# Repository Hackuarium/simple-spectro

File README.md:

# DIY spectrophotometer

## How to use it ?

Please check the [userguide](docs/5-use) to obtain all the useful information about the user interface.

## Goal of the project

This project was done at the [Hackuarium](http://www.hackuarium.ch/en/) association, a DIY biology hacking-space and open laboratory located in Ecublens (Switzerland). Feel free to [contact us](https://form.jotformeu.com/71600609780354) if you would like additional information or would like to buy a fully built and tested spectrophotometer.

Recently, the open-source and open-hardware community has been involved in the creation of open scientific tools. In this context, a few spectrophotometer projects emerged. However, none of them was sufficiently evolved to be casually used in a laboratory. It is for this reason that we started this project.
Our goal was to create a simple spectrophotometer that measures the
absorbance of a sample for 3 different light colors (red, green, blue), that is
self-contained (battery powered) and displays the result on a LCD screen. In addition, the tool had to be reliable, precise and cheap.

The initial idea was that you could teach spectrophotometry without
having to buy an expensive instrument, since you can find experiments
that do not require a specific light wavelength. This includes
optical density for bacteria culture, determination of a pigment's concentration in
a solution, determination of the kinetic of a reaction and many others.

The device is rather cheap, for you can buy all the components on AliExpress
(but one) and either 3D print or laser cut the case (MDF or acrylic glass). When constructing 10, the price
per spectrophotometer is around $30. However if you want to have a final
product with an aluminium case and PCBs already assembled, the cost would rather be $90 each if you order 20 of them.

## Can we do science with this ?

Before trying to explain how it is done more in detail maybe the first
question that we should answer is : can we do science with this tool?
When thinking about the design of the spectro, we found an light sensor that converts the light energy to frequency and that is linear on a range of nearly 10^6. This means that the luminosity range that we can measure precisely is really big. Only the precision of the component is therefore really promising and shows that we could do something that gives good results.

And indeed, the final product gives really accurate results in fields like:

- [Chemistry](docs/6-applications/chemistry/README.md)
- [Biology](docs/6-applications/biology/README.md)

And other, which you can see on [our lab notebook](experiments/README.md).

## Some of our results

### Patent blue V

To begin we did a very simple experiment that allows to measure the absorbance of solutions containing different known concentrations of patent blue V (E131), a blue pigment that is used in various blue candies.

The result is rather good knowing that the solutions were simply prepared by adding various volumes (0 to 2 mL) of a concentrated pigmented solution with a 1mL seringe to 100mL of water. Not the most accurate method...

### Escherichia coli

Another feature of the simple-spectrophotometer is that it works on a rechargeable battery (autonomy of 48 hours). Consequently, you can measure a kinetic by placing the device directly inside an incubator, which is not feasible with a regular commercial spectrophotometer.

Optical density (OD) at 600nm is often used in biology to determine the biomass increase versus time. In this experiment we have placed Escherichia coli with cell growing media directly in the spectrophotometer cuvette and placed the spectrophotometer itself on a shaker in the incubator.
We can then program it to measure the absorbance every X seconds. In our case we measured the absorbance every 30 minutes (up to 40 measures). The following curve was obtained.

This experiment clearly shows the log phase and the stationary phase. But the growth was faster than expected. An acquisition every 15 minutes would have been a better choice.

## Using the simple spectrophotometer to teach science

The use of the spectrophotometer is rather simple. Just put a blank, press the button, wait 10s and put the sample. The result is displayed on the screen. In addition, it could be open so that students could see how it is inside and could really understand how the tool works (avoiding the "black box" effect). Also, since it is inexpensive, having ten of these for a classroom would be possible, which would allow students to have one instrument per pair.

[Using the spectrophotometer](https://www.youtube.com/watch?v=ZfckWQn0Nws)

For all this reason, we also consider our instrument as a pedagogical tool. This allowed us to use it to teach some basic scientific concepts to groups of children and teenagers.

[School in Mondomo (Colombia)](https://www.youtube.com/watch?v=Be6p4-nW06k)

## How to make it ?

The electronic design is compatible with the Arduino platform. We use an
ATMEGA32U4 microcontroller which is directly connected to the peripherals we need for this spectrophotometer.

We prefer to design the full PCB rather than to make a shield for an existing Arduino board. Indeed, the extra work to add the microcontroller is rather limited, so it does not make sense from our point of view to create a shield. Also, the resulting board is smaller and more reliable.

All the components we use but one are mainstream and can be found on eBay or AliExpress. The only special component is the light to frequency converter [TSL235R](https://www.sparkfun.com/datasheets/Sensors/Imaging/TSL235R-LF.pdf)
that we buy on [Mouser website](http://www.mouser.com).

For more details about the construction process, follow one of the links underneath.

- [The PCB](docs/1-pcb) (using eagle)
- [The case](docs/2-case) (using FreeCAD and OpenSCAD)
- [The software](docs/3-software) (using Arduino)

## Experiments

- [Bacteria growth](experiments/bacteria/README.md)
- [Pigment concentration](experiments/color/README.md)
- [Measure of the fluorescence](experiments/fluorescence/README.md)
- [Kinetic of a reaction](experiments/kinetic/README.md)

## Tests

Underneath, you will find some of the tests we have run to verify the quality of our spectrophotometer.

- [Battery](docs/4-tests/battery)
- [Reproducibility of results](docs/4-tests/stability)

# Workshop

We regularly organize one day workshops "Build your own spectrophotometer" during which the participants learn all the process we went through to obtain the final product and build their own spectrophotometer. Please [contact us](https://form.jotformeu.com/71600609780354) if you are interested by this kind of workshop.

Here are the slides of the presentation we make during the workshop.

- [Slides](docs/7-misc/workshop/slides.pdf)

## Cloning the project

This project uses SUBMODULES.

In order to clone it use:

`git clone --recurse-submodules https://github.com/hackuarium/simple-spectro`

To update the submodules:

`git submodule update --recursive --remote`

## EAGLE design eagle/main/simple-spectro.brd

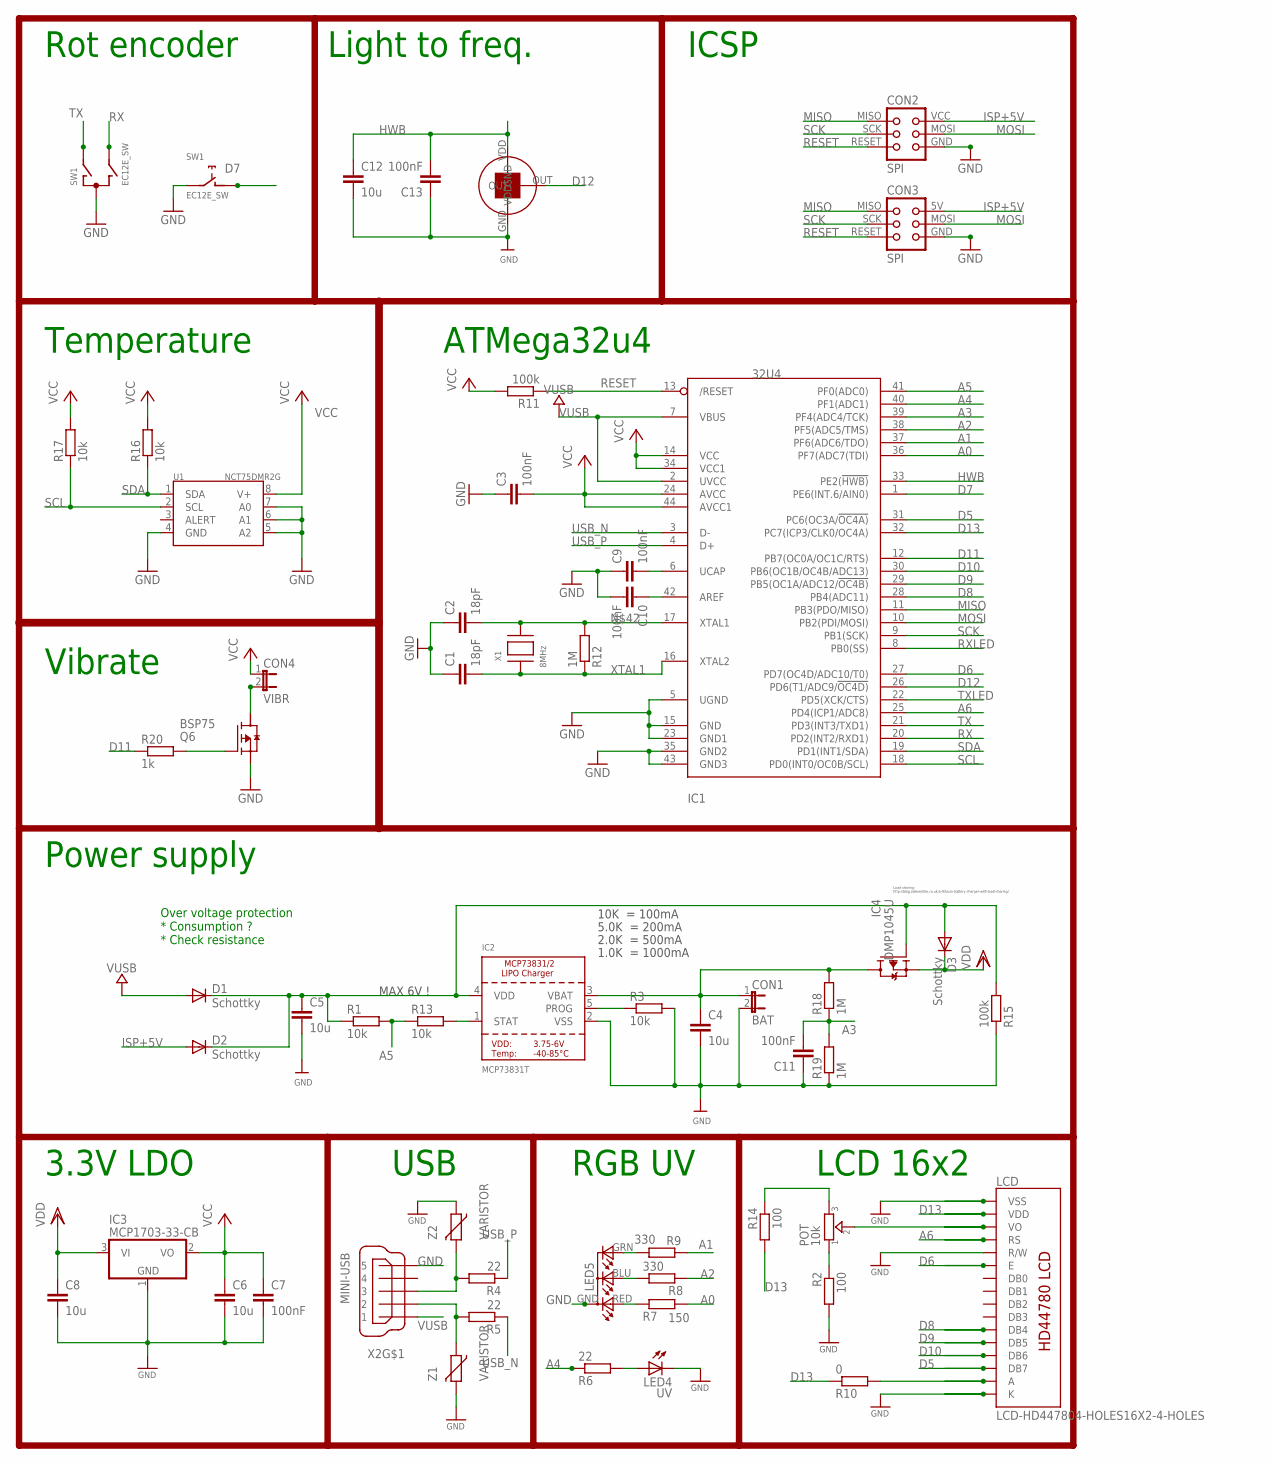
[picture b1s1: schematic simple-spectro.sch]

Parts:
C1, C2: 18pF; C0805K; MPN 77-VJ1206A180JXXPBC; LCSC C1797
C3, C7, C9, C10, C11, C13: 100nF; C0805K; MPN 80-C1206C104K5R; LCSC C49678
C4, C5, C6, C8, C12: 10u; C0805K; MPN 77-VJ1206V106ZXQTBC; LCSC C15850
CON1: BAT; JP1
CON2: SPI; TINYISP
CON3: SPI; TC2030-MCP-NL
CON4: VIBR; JP1
D1, D2, D3: Schottky; SOD123; MPN 621-1N5819HW-F; LCSC C82544
IC1: 32U4; TQFP44; MPN 556-ATMEGA32U4RC-AU; LCSC C44854
IC2: MCP73831T; SOT23-5; MPN 579-MCP73831T-3ACIOT; LCSC C14879
IC3: MCP1703-33-CB; SOT23; LCSC C53352
IC4: DMP1045U; SOT-23; MPN 621-DMP1045U-7; LCSC C110499
LCD: LCD-HD447804-HOLES16X2-4-HOLES; LCD-16X2-4HOLES
LED4: UV; LED5MM
LED5: RGB-COMMON-CATHODE; LED-TRICOLOR-THROUGHHOLE
POT: 10k; TRIMMER_3362P
Q6: BSP75; PG-SOT-223
R1, R3, R13, R16, R17: 10k; R0805; LCSC C17414
R2, R14: 100; R0805; LCSC C17408
R4, R5: 22; R0805; LCSC C17561
R6: 22; R0805; MPN 667-ERJ-8GEYJ101V; LCSC C17561
R7: 150; R0805; LCSC C17513
R8, R9: 330; R0805; LCSC C17513
R10: 0; R0805; LCSC C17477
R11, R15: 100k; R0805; MPN RC1206FR-07100KL; LCSC C17407
R12, R18, R19: 1M; R0805; LCSC C17514
R20: 1k; R0805; LCSC C17513
SW1: EC12E_SW; ALPS_EC12E_SW
U1: NCT75DMR2G; MSOP8; LCSC C94387
U$7: TSL237
X1: 8MHz; NX6035; MPN 729-F60800010; LCSC C122522
X2: MINI-USB; 32005-201; MPN 649-10033526-N3212LF; LCSC C46391
Z1, Z2: VARISTOR; CT/CN0603; LCSC C126845

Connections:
A0: IC1.36 (PF7(ADC7(TDI)), R7.2
A1: IC1.37 (PF6(ADC6/TDO)), R9.1
A2: IC1.38 (PF5(ADC5/TMS)), R8.2
A3: C11.2, IC1.39 (PF4(ADC4/TCK)), R18.1, R19.2
A4: IC1.40 (PF1(ADC1)), R6.1
A5: IC1.41 (PF0(ADC0)), R1.2, R13.1
A6: IC1.25 (PD4(ICP1/ADC8)), LCD.4 (RS)
AREF: C10.1, IC1.42 (AREF)
D5: IC1.31 (PC6(OC3A/!OC4A)), LCD.14 (DB7)
D6: IC1.27 (PD7(OC4D/ADC10/T0)), LCD.6 (E)
D7: IC1.1 (PE6(INT.6/AIN0)), SW1.D (1)
D8: IC1.28 (PB4(ADC11)), LCD.11 (DB4)
D9: IC1.29 (PB5(OC1A/ADC12/!OC4B)), LCD.12 (DB5)
D10: IC1.30 (PB6(OC1B/OC4B/ADC13)), LCD.13 (DB6)
D11: IC1.12 (PB7(OC0A/OC1C/RTS)), R20.1
D12: IC1.26 (PD6(T1/ADC9/!OC4D)), U$7.OUT
D13: IC1.32 (PC7(ICP3/CLK0/OC4A)), LCD.2 (VDD), R10.1, R14.2
GND: C1.1, C2.1, C3.1, C4.2, C5.2, C6.2, C7.2, C8.2, C9.1, C10.2, C11.1, C12.2, C13.1, CON1.2, CON2.GND, CON3.GND, IC1.5 (UGND), IC1.15 (GND), IC1.23 (GND1), IC1.35 (GND2), IC1.43 (GND3), IC2.2 (VSS), IC3.1 (GND), LCD.1 (VSS), LCD.5 (R/W), LCD.16 (K), LED4.K (C), LED5.GND (A2), Q6.3 (S), R2.2, R3.2, R15.1, R19.1, SW1.C, SW1.E (2), U1.4 (GND), U1.5 (A2), U1.6 (A1), U1.7 (A0), U$7.GND, X2.5, Z1.2, Z2.1
HWB: C12.1, C13.2, IC1.33 (PE2(!HWB)), U$7.VDD
ISP+5V: CON2.VCC, CON3.5V (VCC), D2.A
MISO: CON2.MISO, CON3.MISO, IC1.11 (PB3(PDO/MISO))
MOSI: CON2.MOSI, CON3.MOSI, IC1.10 (PB2(PDI/MOSI))
unnamed: C9.2, IC1.6 (UCAP)
unnamed: LCD.3 (VO), POT.2
unnamed: LED4.A, R6.2
unnamed: POT.1, R2.1
unnamed: IC2.1 (STAT), R13.2
unnamed: IC2.5 (PROG), R3.1
unnamed: Q6.1 (G), R20.2
unnamed: LED5.GRN (CGREEN), R9.2
unnamed: LED5.BLU (CBLUE), R8.1
unnamed: LCD.15 (A), R10.2
unnamed: POT.3, R14.1
unnamed: LED5.RED (CRED), R7.1
unnamed: CON4.2, Q6.2 (D)
unnamed: C5.1, D1.C, D2.C, D3.A, IC2.4 (VDD), IC4.1 (G), R1.1, R15.2
unnamed: C2.2, IC1.17 (XTAL1), R12.2, X1.P$2
RESET: CON2.RESET, CON3.RESET, IC1.13 (/RESET), R11.1
RX: IC1.20 (PD2(INT2/RXD1)), SW1.B
RXLED: IC1.8 (PB0(SS))
SCK: CON2.SCK, CON3.SCK, IC1.9 (PB1(SCK))
SCL: IC1.18 (PD0(INT0/OC0B/SCL)), R17.1, U1.2 (SCL)
SDA: IC1.19 (PD1(INT1/SDA)), R16.1, U1.1 (SDA)
TX: IC1.21 (PD3(INT3/TXD1)), SW1.A
TXLED: IC1.22 (PD5(XCK/CTS))
USBC_N: R5.2, X2.2, Z1.1
USBC_P: R4.2, X2.3, Z2.2
USB_N: IC1.3 (D-), R5.1
USB_P: IC1.4 (D+), R4.1
VBAT1: C4.1, CON1.1, IC2.3 (VBAT), IC4.3 (D), R18.2
VCC: C3.2, C6.1, C7.1, CON4.1, IC1.14 (VCC), IC1.24 (AVCC), IC1.34 (VCC1), IC1.44 (AVCC1), IC3.2 (VO), R11.2, R16.2, R17.2, U1.8 (V+)
VDD: C8.1, D3.C, IC3.3 (VI), IC4.2 (S)
VUSB: D1.A, IC1.2 (UVCC), IC1.7 (VBUS), X2.1
XTAL1: C1.2, IC1.16 (XTAL2), R12.1, X1.P$1

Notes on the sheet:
USB
ICSP
ATMega32u4
LCD 16x2
Rot encoder
3.3V LDO
10K = 100mA
5.0K = 200mA
2.0K = 500mA
1.0K = 1000mA
MAX 6V !
Load sharing: http://blog.zakkemble.co.uk/a-lithium-battery-charger-with-load-sharing/
RGB UV
Over voltage protection * Consumption ? * Check resistance
Light to freq.
Power supply
Temperature
Vibrate

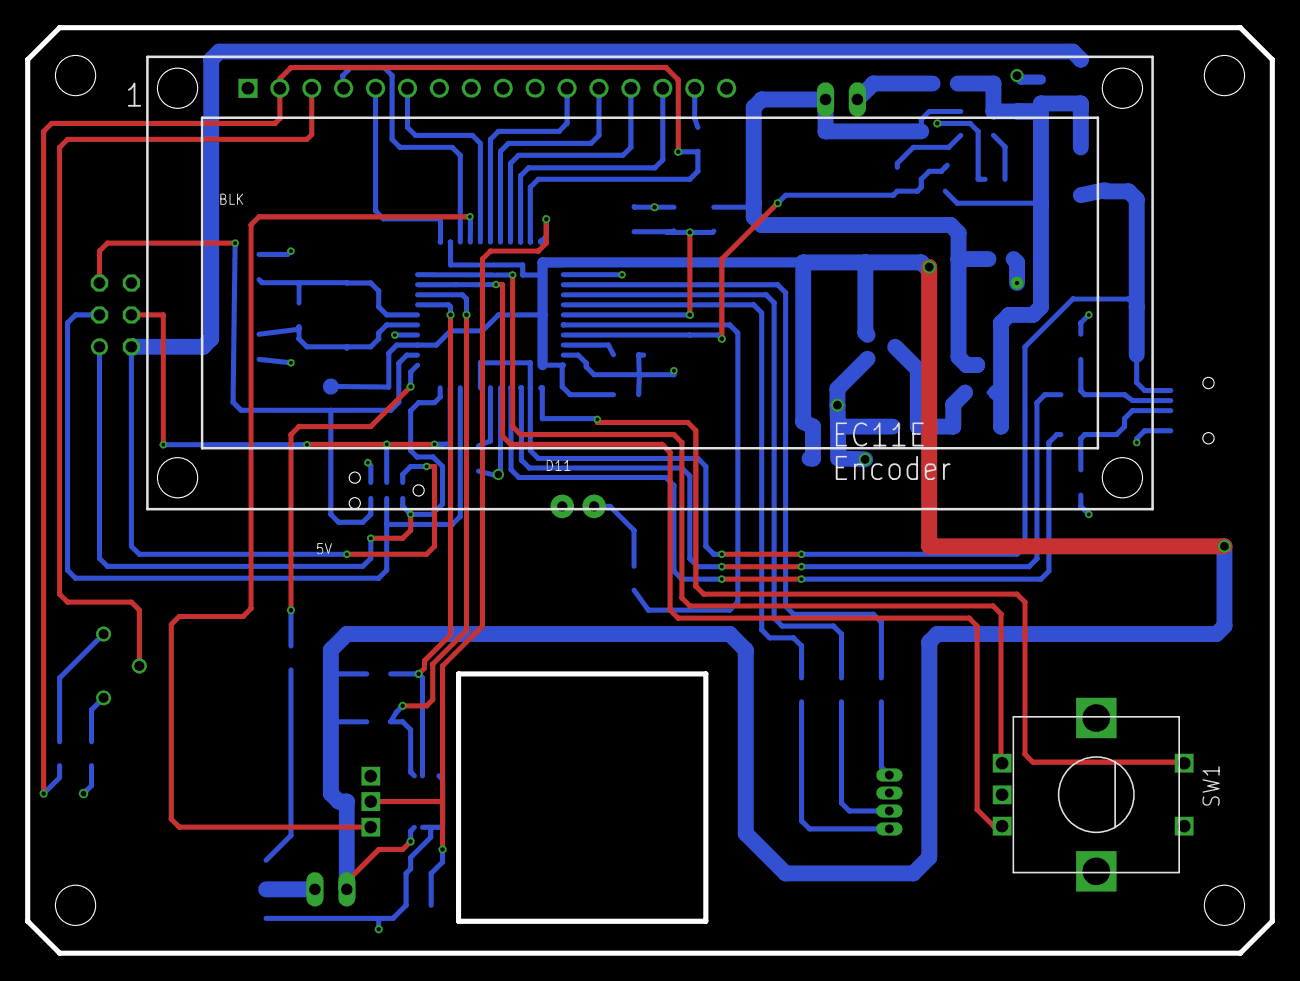
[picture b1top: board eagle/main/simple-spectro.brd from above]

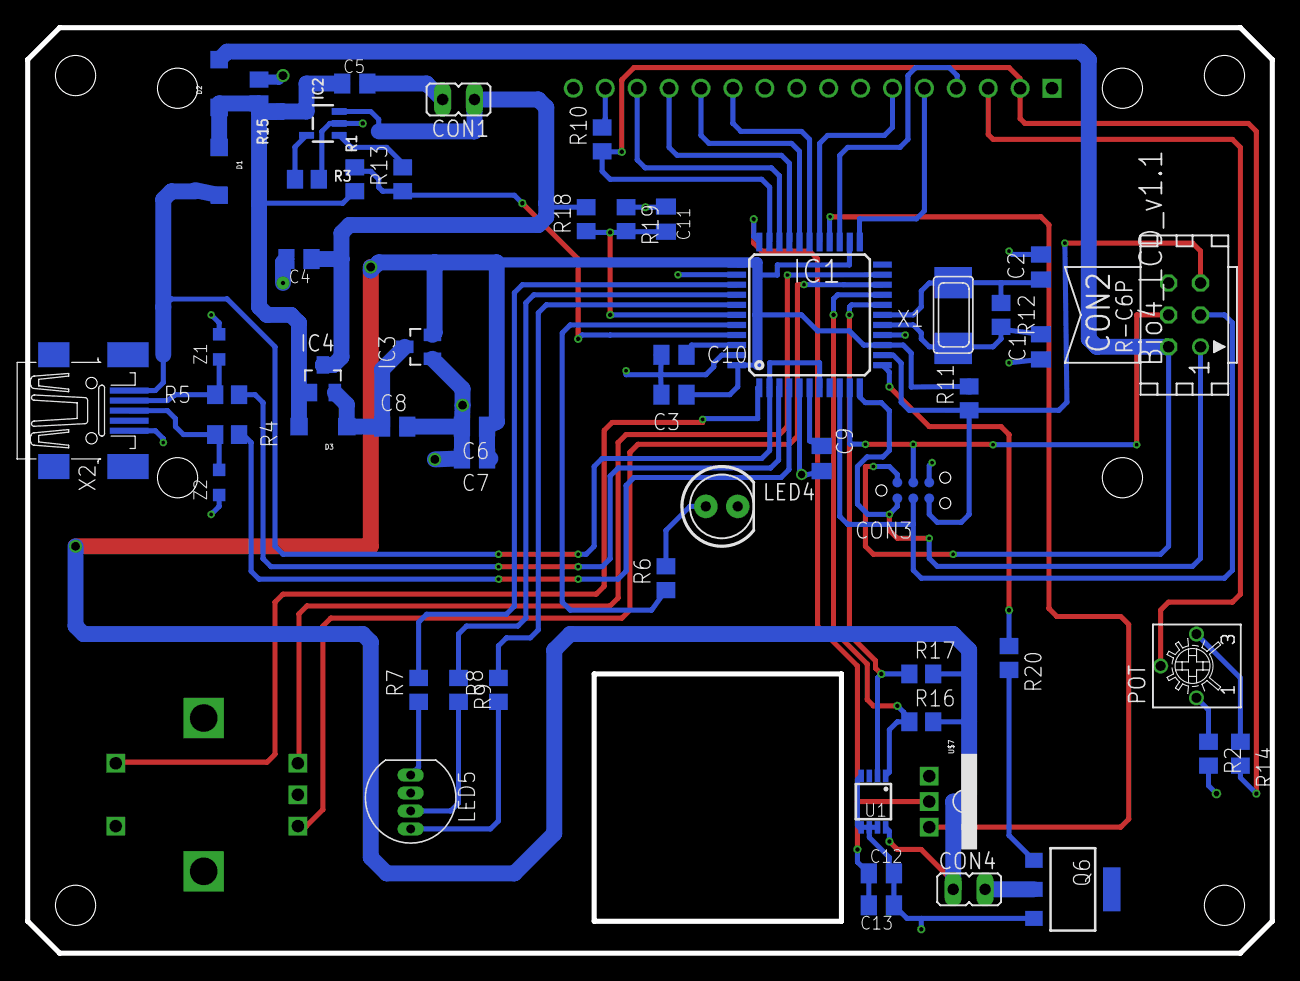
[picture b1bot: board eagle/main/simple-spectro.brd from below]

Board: 2 copper layers, 99.1 x 73.7 mm, 56 parts (54 on the bottom side), 52 nets.

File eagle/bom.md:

| Kind            |  Value         |  Package  |  Qty  |
| ----------------|----------------|-----------|-------  |
| Capacitor       |  100nF         |  1206     |  4  |
| Capacitor       |  10u           |  1206     |  4  |
| Capacitor       |  22pF          |  1206     |  2  |
| Connector       |  BAT           |  2.54mm   |  1  |
| Crystal         |  8MHz          |  6035     |  1  |
| ICSP            |  ICSP          |  2 x 3, 2.54mm  |  1  |
| ICSP            |  TINYISP       |  Tag connect  |  1  |
| Jumper          |  Jumper        |  2.54mm   |  2  |
| LCD             |  LCD-HD447804  |  16x1 2.54mm  |  1  |
| Led             |  GREEN         |  1206     |  1  |
| Led             |  RED           |  1206     |  2  |
| Led             |  RGB-COMMON-CATHODE  |  RGB 5mm led  |  1  |
| Led             |  UV            |  5mm      |  1  |
| Led             |  UV            |  3mm      |  1  |
| Light detector  |  TSL237        |  3x1 2.54mm  |  1  |
| LiPo charger    |  MCP73831T     |  SOT23-5  |  1  |
| Microcontroller |  ATMEGA32U4-AU |  TQFP44  |  1  |
| Mini USB        |  MINI-USB      |  32005-201  |  1  |
| Regulator       |  MCP1703-33    |  SOT223  |  1  |
| Resistor        |  22            |  1206  |  2  |
| Resistor        |  100           |  1206  |  1  |
| Resistor        |  150           |  1206  |  2  |
| Resistor        |  220           |  1206  |  1  |
| Resistor        |  470           |  1206  |  2  |
| Resistor        |  100k          |  1206  |  2  |
| Resistor        |  10k           |  1206  |  2  |
| Resistor        |  1k            |  1206  |  3  |
| Resistor        |  1M            |  1206  |  1  |
| Rotary Encoder  |  EC11E         |  EC11E    |  1  |
| Schottky        |  1N581         |  1206  |  2  |
| Transistor      |  DMP1045U      |  SOT-23  |  1  |
| Trimmer         |  10k           |  3362P  |  1  |

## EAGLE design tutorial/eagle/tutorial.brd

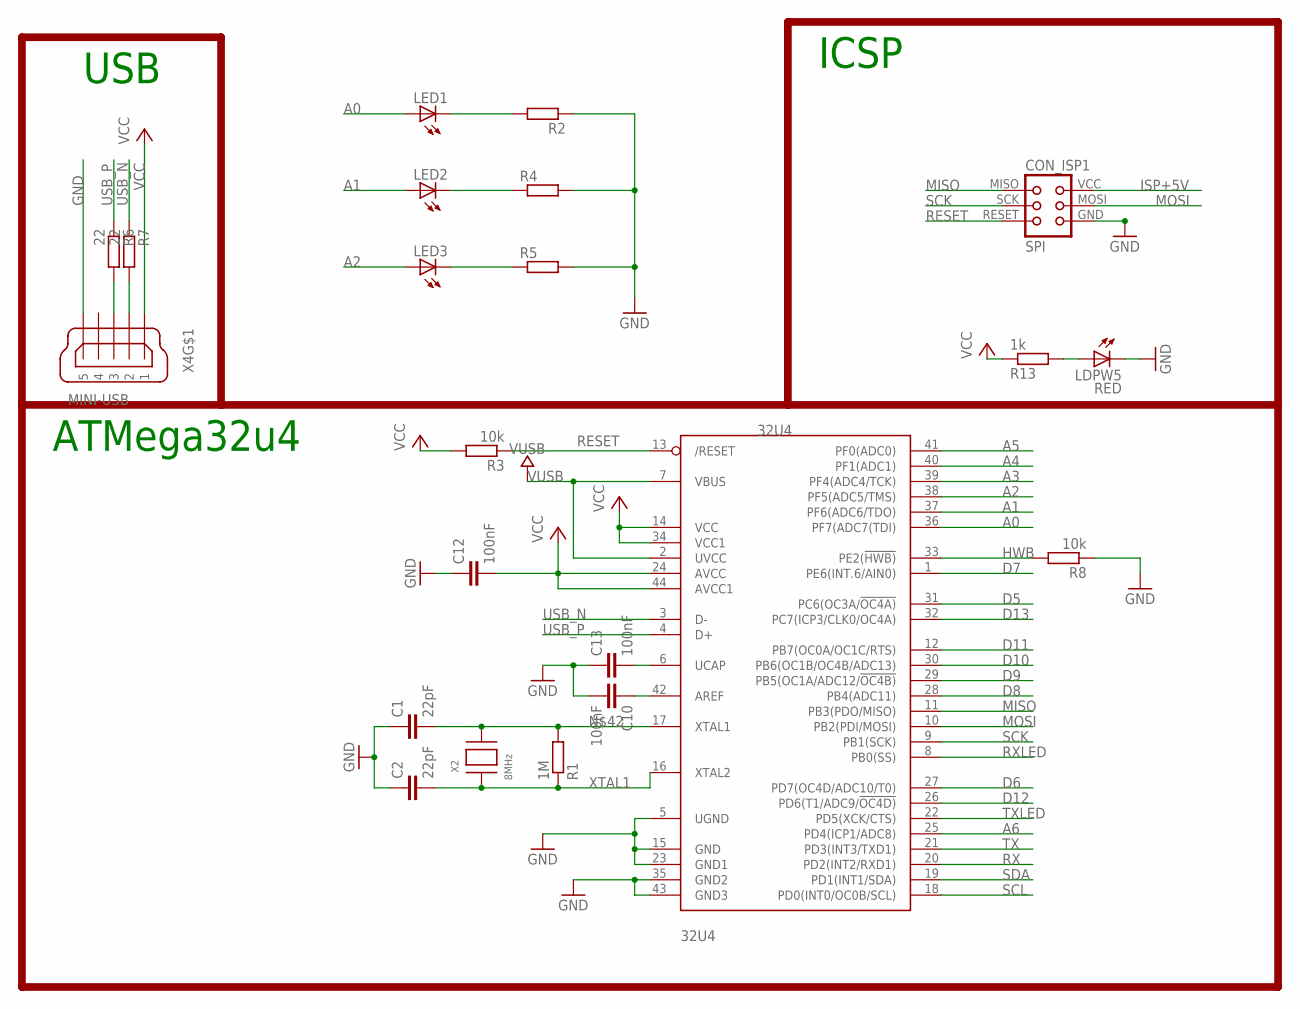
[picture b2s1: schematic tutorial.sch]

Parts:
32U4: 32U4; TQFP44
C1, C2: 22pF; C1206
C10, C12, C13: 100nF; C1206
CON_ISP1: SPI; TINYISP
LDPW5: RED; LED-1206
LED1, LED2, LED3: LED5MM
R1: 1M; M1206
R2: R-EU_R1206; R1206; LCSC 12345
R3, R8: 10k; M1206
R4, R5: R-EU_R1206; R1206
R6, R7: 22; M1206
R13: 1k; M1206
X2: 8MHz; NX6035
X4: MINI-USB; 32005-201

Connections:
A0: 32U4.36 (PF7(ADC7(TDI)), LED1.A
A1: 32U4.37 (PF6(ADC6/TDO)), LED2.A
A2: 32U4.38 (PF5(ADC5/TMS)), LED3.A
A3: 32U4.39 (PF4(ADC4/TCK))
A4: 32U4.40 (PF1(ADC1))
A5: 32U4.41 (PF0(ADC0))
A6: 32U4.25 (PD4(ICP1/ADC8))
AREF: 32U4.42 (AREF), C10.1
D5: 32U4.31 (PC6(OC3A/!OC4A))
D6: 32U4.27 (PD7(OC4D/ADC10/T0))
D7: 32U4.1 (PE6(INT.6/AIN0))
D8: 32U4.28 (PB4(ADC11))
D9: 32U4.29 (PB5(OC1A/ADC12/!OC4B))
D10: 32U4.30 (PB6(OC1B/OC4B/ADC13))
D11: 32U4.12 (PB7(OC0A/OC1C/RTS))
D12: 32U4.26 (PD6(T1/ADC9/!OC4D))
D13: 32U4.32 (PC7(ICP3/CLK0/OC4A))
GND: 32U4.5 (UGND), 32U4.15 (GND), 32U4.23 (GND1), 32U4.35 (GND2), 32U4.43 (GND3), C1.1, C2.1, C10.2, C12.1, C13.1, CON_ISP1.GND, LDPW5.C, R2.1, R4.2, R5.2, R8.1, X4.5
HWB: 32U4.33 (PE2(!HWB)), R8.2
ISP+5V: CON_ISP1.VCC
MISO: 32U4.11 (PB3(PDO/MISO)), CON_ISP1.MISO
MOSI: 32U4.10 (PB2(PDI/MOSI)), CON_ISP1.MOSI
unnamed: 32U4.6 (UCAP), C13.2
unnamed: LED3.K (C), R5.1
unnamed: LED2.K (C), R4.1
unnamed: LED1.K (C), R2.2
unnamed: LDPW5.A, R13.2
unnamed: 32U4.17 (XTAL1), C1.2, R1.2, X2.P$2
RESET: 32U4.13 (/RESET), CON_ISP1.RESET, R3.1
RX: 32U4.20 (PD2(INT2/RXD1))
RXLED: 32U4.8 (PB0(SS))
SCK: 32U4.9 (PB1(SCK)), CON_ISP1.SCK
SCL: 32U4.18 (PD0(INT0/OC0B/SCL))
SDA: 32U4.19 (PD1(INT1/SDA))
TX: 32U4.21 (PD3(INT3/TXD1))
TXLED: 32U4.22 (PD5(XCK/CTS))
USBC_N: R7.2, X4.2
USBC_P: R6.2, X4.3
USB_N: 32U4.3 (D-), R7.1
USB_P: 32U4.4 (D+), R6.1
VCC: 32U4.14 (VCC), 32U4.24 (AVCC), 32U4.34 (VCC1), 32U4.44 (AVCC1), C12.2, R3.2, R13.1, X4.1
VUSB: 32U4.2 (UVCC), 32U4.7 (VBUS)
XTAL1: 32U4.16 (XTAL2), C2.2, R1.1, X2.P$1

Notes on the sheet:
USB
ICSP
ATMega32u4

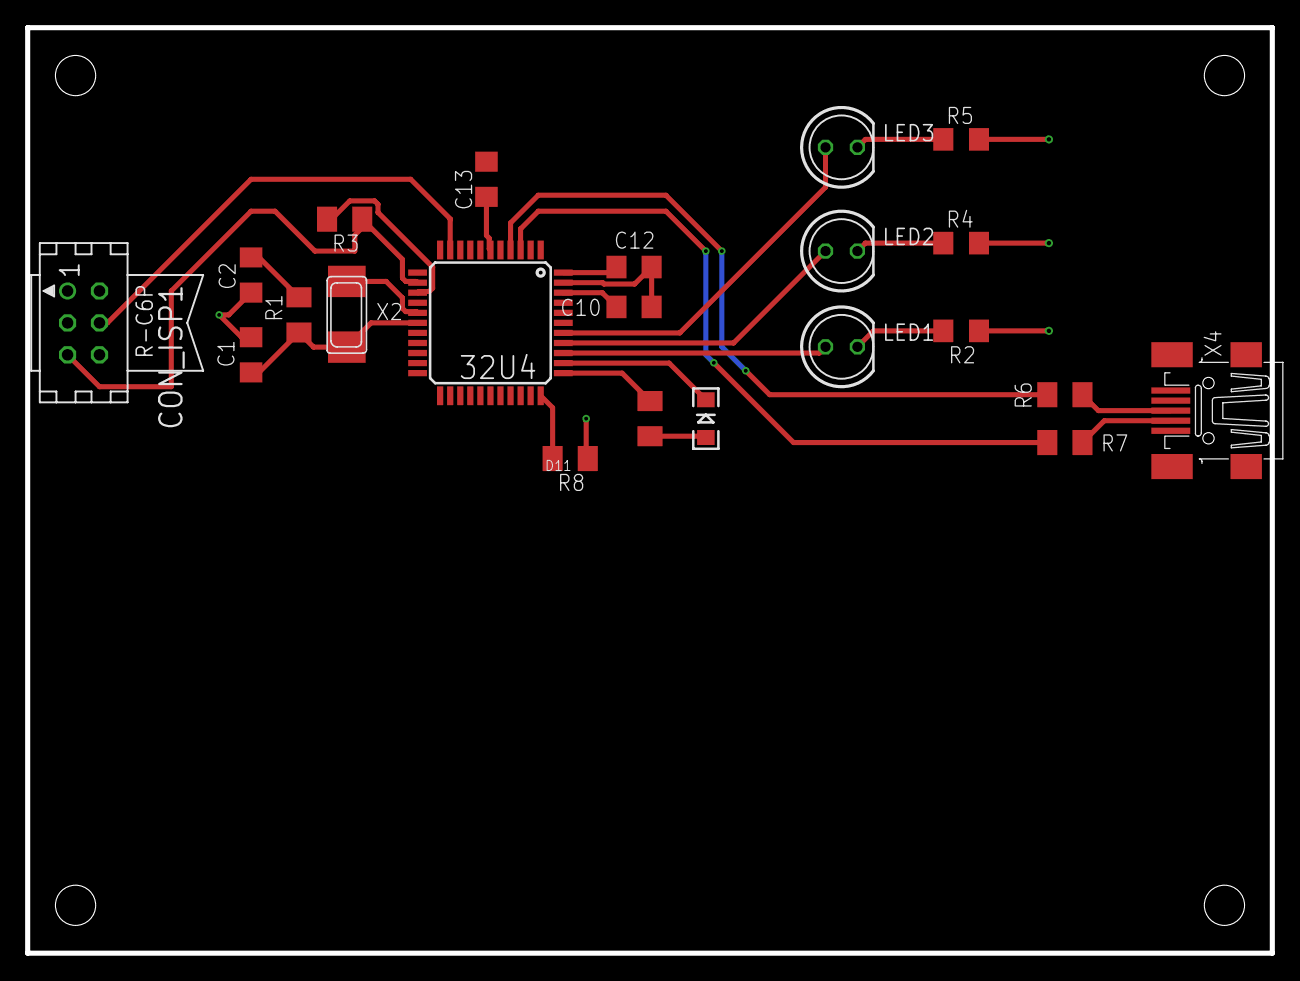
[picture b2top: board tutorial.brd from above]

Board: 2 copper layers, 99.1 x 73.7 mm, 22 parts (0 on the bottom side), 23 nets.

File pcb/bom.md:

| Kind            |  Value         |  Package        |  Qty  |
| ----------------|----------------|-----------------|-------|
| Battery         |  LiPo 4.2v     |                 |  1    |
| Capacitor       |  100nF         |  1206           |  6    | x
| Capacitor       |  10u           |  1206           |  5    | x
| Capacitor       |  18pF          |  1206           |  2    | x
| Connector       |  BAT           |  2.54mm         |  1    | x
| Crystal         |  8MHz          |  6035           |  1    | x
| ICSP            |  ICSP          |  2 x 3, 2.54mm  |  1    | -
| ICSP            |  TINYISP       |  Tag connect    |  1    | x
| Jumper          |  Jumper        |  2.54mm         |  2    | x
| LCD             |  LCD-HD447804  |  16x1 2.54mm    |  1    | 8
| Led             |  GREEN         |  1206           |  1    | x
| Led             |  RGB-COMMON-CAT|  RGB 5mm led    |  1    |
| Led             |  Blue          |  5mm            |  1    |
| Led             |  Blue / Violet |  3mm            |  1    |
| Light detector  |  TSL237        |  3x1 2.54mm     |  1    |
| LiPo charger    |  MCP73831T     |  SOT23-5        |  1    | x
| Microcontroller |  ATMEGA32U4-AU |  TQFP44         |  1    |
| Mini USB        |  MINI-USB      |  32005-201      |  1    | x  
| Power switch    |  BSP75         |  SOT223         |  1    |
| Regulator       |  MCP1703-33    |  SOT223         |  1    | x
| Resistor        |  0             |  1206           |  1    |
| Resistor        |  22            |  1206           |  3    | x
| Resistor        |  100           |  1206           |  1    | x
| Resistor        |  220           |  1206           |  1    | x
| Resistor        |  100k          |  1206           |  2    | x
| Resistor        |  10k           |  1206           |  5    | x
| Resistor        |  1k            |  1206           |  4    | x
| Resistor        |  1M            |  1206           |  3    | x
| Rotary Encoder  |  EC11E         |  EC11E          |  1    | 9
| Schottky        |  1N5817        |  1206           |  2    | x
| T° sensor       |  NCT175DMR2G   |  Micro8         |  1    |
| Transistor      |  DMP1045U      |  SOT-23         |  1    | x
| Trimmer         |  10k           |  3362P          |  1    | x

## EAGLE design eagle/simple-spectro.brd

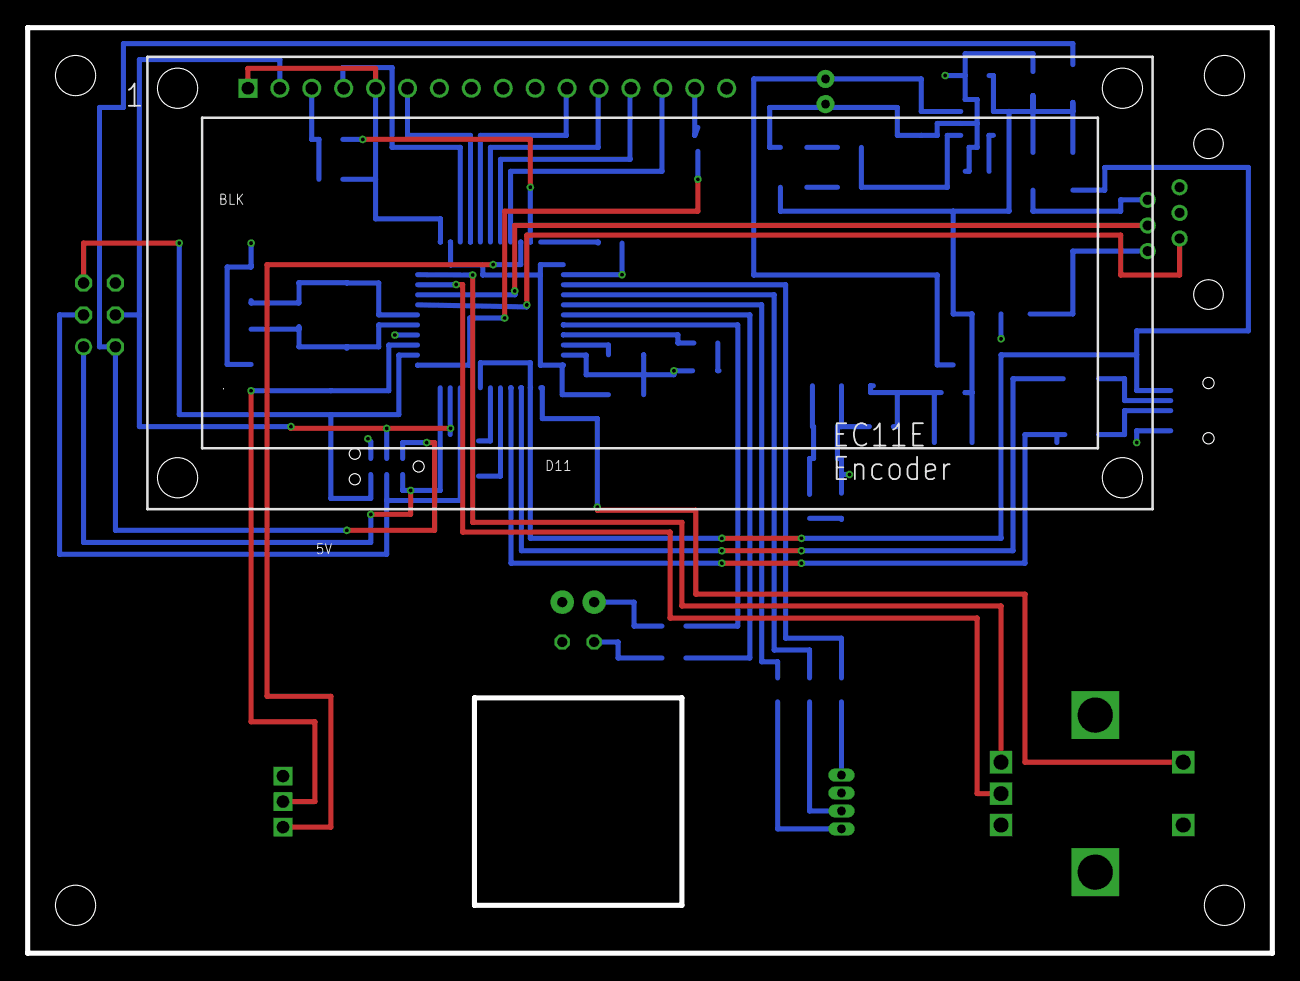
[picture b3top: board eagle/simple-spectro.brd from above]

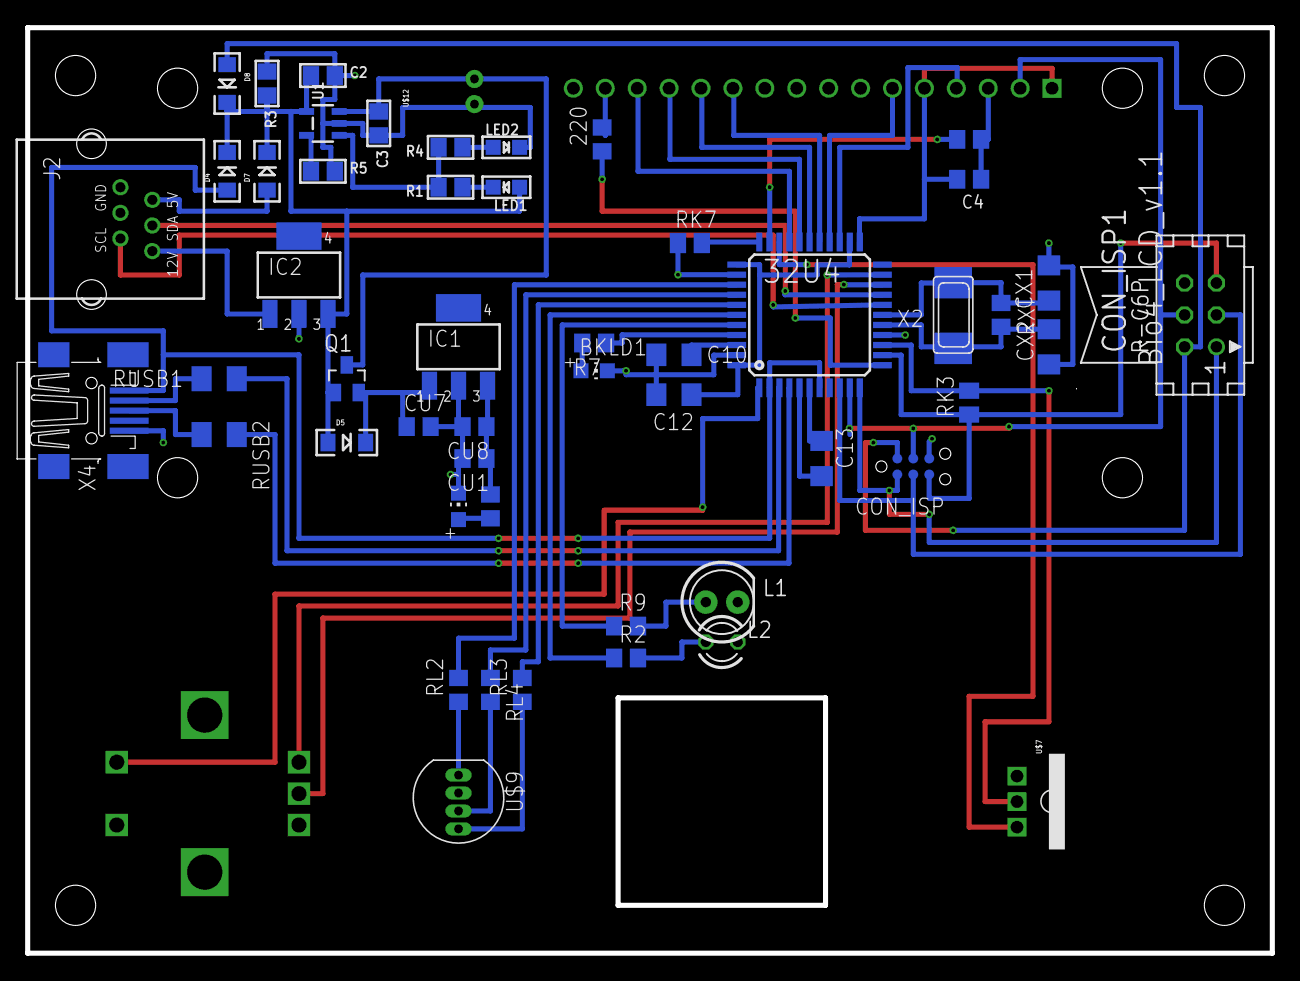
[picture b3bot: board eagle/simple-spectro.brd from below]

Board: 4 copper layers, 99.1 x 73.7 mm, 54 parts (52 on the bottom side), 55 nets.

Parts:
32U4: 32U4; TQFP44
220: 220; R0805
BKLD1: RED; CHIP-LED0805
C2, C3: 10µF; 0805
C4: 100nF; C805
C10, C12, C13: 100nF; C1206
CON_ISP: SPI; TC2030-MCP-NL
CON_ISP1: SPI; TINYISP
CU1: 100nF; C0805
CU7, CU8: 10u; C0805
CX1, CX2: 22pF; C1206
D4, D5, D7, D8: 1N581D1206; LED-1206
IC1: MCP1703-33; SOT223
IC2: MCP1703-50; SOT223
J2: RJ12RIGHTANGLE-I2C; RJ12-RIGHTANGLE-I2C
L1: UV; LED5MM
L2: UV; LED3MM
LDPW5: RED; CHIP-LED0805
LED1: RED; CHIPLED_0805
LED2: GREEN; CHIPLED_0805
Q1: DMP1045U; SOT-23
R1, R4: 470; 0805
R2, R7, R9, R13: 1k; R0805
R3: 100k; 0805
R5: 10K\; 0805
RK1: 3.9k; R0805
RK3: 100k; M0805
RK7: 10k; M0805
RL2, RL4: 150; R0805
RL3: 100; R0805
RUSB1, RUSB2: 22; M1206
RXT: 1M; R0805
U1: MCP73831T; SOT23-5
U$1: EC11E
U$7: TSL237
U$9: RGB-COMMON-CATHODE; LED-TRICOLOR-THROUGHHOLE
U$11: LCD-HD447804-HOLES16X2-4-HOLES; LCD-16X2-4HOLES
U$12: CONN2; JST-2-XH
X2: 8MHz; NX6035
X4: MINI-USB; 32005-201

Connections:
A0: 32U4.36, RL2.2
A1: 32U4.37, RL4.1
A2: 32U4.38, RL3.2
A3: 32U4.39, R2.1
A4: 32U4.40, R9.1
A5: 32U4.41, R7.1
A6: 32U4.25, U$11.4
AREF: 32U4.42, C10.1
D5*: 32U4.31, U$7.OUT
D6*: 32U4.27, U$11.11
D7*: 32U4.1, U$1.D
D8*: 32U4.28, U$11.12
D9*: 32U4.29, U$11.13
D10*: 32U4.30, U$11.14
D11*: 32U4.12, 220.1
D12*: 32U4.26, U$11.6
D13*: 32U4.32, RK1.1
GND: 32U4.5, 32U4.15, 32U4.23, 32U4.35, 32U4.43, BKLD1.C, C2.2, C3.2, C4.2, C10.2, C12.1, C13.1, CON_ISP.GND, CON_ISP1.GND, CU1.2, CU7.2, CU8.2, CX1.1, CX2.1, IC1.2, IC2.2, J2.GND1, J2.GND2, L1.K, L2.K, LDPW5.C, LED2.C, R3.1, R5.2, RK7.1, U1.2, U$1.C, U$1.E, U$7.GND, U$9.GND, U$11.1, U$11.5, U$11.16, U$12.1, X4.5
HWB: 32U4.33, RK7.2
I2C+5V: D7.A, J2.+5V
I2C+12V: IC2.1, J2.+12V
ISP+5V: CON_ISP.5V, CON_ISP1.VCC, D8.A
MISO: 32U4.11, CON_ISP.MISO, CON_ISP1.MISO
MOSI: 32U4.10, CON_ISP.MOSI, CON_ISP1.MOSI, U$11.2
unnamed: 32U4.6, C13.2
unnamed: C4.1, RK1.2, U$11.3
unnamed: L1.A, R9.2
unnamed: LED1.C, R1.1
unnamed: R1.2, R4.2, U1.1
unnamed: R5.1, U1.5
unnamed: LED2.A, R4.1
unnamed: L2.A, R2.2
unnamed: RL4.2, U$9.GRN
unnamed: RL3.1, U$9.BLU
unnamed: 220.2, U$11.15
unnamed: LDPW5.A, R13.2
unnamed: RL2.1, U$9.RED
unnamed: BKLD1.A, R7.2
unnamed: C2.1, D4.C, D5.A, D7.C, D8.C, IC2.3, LED1.A, Q1.1, R3.2, U1.4
unnamed: 32U4.17, CX1.2, RXT.2, X2.P$2
RESET: 32U4.13, CON_ISP.RESET, CON_ISP1.RESET, RK3.1
RX: 32U4.20, U$1.B
SCK: 32U4.9, CON_ISP.SCK, CON_ISP1.SCK
SCL: 32U4.18, J2.SCL
SDA: 32U4.19, J2.SDA
TX: 32U4.21, U$1.A
USBC_N: RUSB1.2, X4.2
USBC_P: RUSB2.2, X4.3
USB_N: 32U4.3, RUSB1.1
USB_P: 32U4.4, RUSB2.1
VBAT1: C3.1, Q1.3, U1.3, U$12.2
VCC: 32U4.14, 32U4.24, 32U4.34, 32U4.44, C12.2, CU1.1, CU8.1, IC1.3, R13.1, RK3.2, U$7.VDD
VDD: CU7.1, D5.C, IC1.1, Q1.2
VUSB: 32U4.2, 32U4.7, D4.A, X4.1
XTAL1: 32U4.16, CX2.2, RXT.1, X2.P$1

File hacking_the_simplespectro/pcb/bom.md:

| Kind            |  Value         |  Package        |  Qty  |
| ----------------|----------------|-----------------|-------|
| Battery         |  LiPo 4.2v     |                 |  1    |
| Capacitor       |  100nF         |  1206           |  6    | x
| Capacitor       |  10u           |  1206           |  5    | x
| Capacitor       |  18pF          |  1206           |  2    | x
| Connector       |  BAT           |  2.54mm         |  1    | x
| Crystal         |  8MHz          |  6035           |  1    | x
| ICSP            |  ICSP          |  2 x 3, 2.54mm  |  1    | -
| ICSP            |  TINYISP       |  Tag connect    |  1    | x
| Jumper          |  Jumper        |  2.54mm         |  2    | x
| LCD             |  LCD-HD447804  |  16x1 2.54mm    |  1    | 8
| Led             |  GREEN         |  1206           |  1    | x
| Led             |  RGB-COMMON-CAT|  RGB 5mm led    |  1    |
| Led             |  Blue          |  5mm            |  2    |
| Light detector  |  TSL237        |  3x1 2.54mm     |  1    |
| LiPo charger    |  MCP73831T     |  SOT23-5        |  1    | x
| Microcontroller |  ATMEGA32U4-AU |  TQFP44         |  1    |
| Mini USB        |  MINI-USB      |  32005-201      |  1    | x  
| Power switch    |  BSP75         |  SOT223         |  1    |
| Regulator       |  MCP1703-33    |  SOT223         |  1    | x
| Resistor        |  0             |  1206           |  1    |
| Resistor        |  22            |  1206           |  4    | x
| Resistor        |  100           |  1206           |  1    | x
| Resistor        |  220           |  1206           |  1    | x
| Resistor        |  100k          |  1206           |  2    | x
| Resistor        |  10k           |  1206           |  5    | x
| Resistor        |  1k            |  1206           |  1    | x
| Resistor        |  1M            |  1206           |  3    | x
| Rotary Encoder  |  EC11E         |  EC11E          |  1    | 9
| Schottky        |  1N5817        |  1206           |  2    | x
| T° sensor       |  NCT175DMR2G   |  Micro8         |  1    |
| Transistor      |  DMP1045U      |  SOT-23         |  1    | x
| Trimmer         |  10k           |  3362P          |  1    | x

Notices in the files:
parts and their libraries:
lpatiny: ©2009 ROFA.cz - modified and updated by Robert Darlington ‹rdarlington@gmail.com›
microbuilder: This work is placed in the public domain, and may be freely used for commercial and non-commercial work with the following conditions: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
